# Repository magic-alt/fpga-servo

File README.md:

# fpga-servo

FPGA-based single-axis PMSM/BLDC servo-drive daughterboard for the ALINX AX7010 / Zynq-7000 (2022 board, active PL connector J10).

> **Four-layer engineering CAD — 2026-10-19; manufacturing hold.** Both ADC variants now have synchronized schematics and four-layer PCBs, independent BOMs and portable local libraries/models. Current candidates have zero native ERC/DRC violations, unconnected items and schematic-parity differences; eight Kelvin paths, bounded package escapes, free-corner checks, whole-board reserved-ground-layer checks and maximum ADC-body digital-copper exclusion pass. These are CAD results. Human engineering reviews and exact material/manufacturing-process acceptance remain open; neither board is approved for fabrication or full-power operation. See the [dual-board review](docs/reviews/dual_prototype_2026-10-18/README.md) and [release gates](docs/release_gates.md).

## 两种 ADC 方案

原方案使用 **ADS8588SIPM**；新方案使用 **AD7606C-16BSTZ**，采用四路 DOUT、电平转换和独立 XDC。AD7606C 的 1 MSPS、0–5 V 高速模式典型相位延迟及读取预算见[选型与迁移规格](docs/adc_high_performance_reselection_2026-10-12.md)和[FPGA 接口草案](hardware/ad7606c_servo/ad7606c_fast_candidate_profile_2026-10-12.json)。这些是器件及接口设计依据，实际闭环带宽仍须由 RTL、时序和整机测量验证。

**当前双方案：** [ADS8588S 原方案](hardware/ads8588s_servo/README.md) 与 [AD7606C 新方案](hardware/ad7606c_servo/README.md) 分目录维护，各有原理图、BOM、XDC 和 PCB。两方案新增独立 DC-link 子页，并修正编码器接收器引脚、栅极电阻和辅助电源；本轮电气 ECO 后两板已完成同步、整板布线及原生 DRC/图板一致性验收；工程签核与材料/特殊工艺接受仍开放。[最终工程审阅包](docs/reviews/dual_prototype_2026-10-18/manufacturing_review_packet.md)记录实际导出、校验和剩余门禁。通过[硬件入口](hardware/README.md)选择工程。

## Rev.A-P prototype design basis

| Item | Current design (not yet qualified) |
| --- | --- |
| Input / switching | DC 24–48 V; 20 kHz six-command PWM from AX7010 PL |
| Current / cooling | 10 A RMS continuous phase; 20 A instantaneous phase amplitude for 30 s, balanced sine (14.142 Arms); repetition/cooldown still to be qualified; 40 °C max ambient; forced air |
| Inverter | Six 100 V BSC040N10NS5 MOSFETs; **non-inverting DRV8300DPWR** with internal bootstrap diodes |
| Current sensing | Three motor-phase 5 mΩ / 3 W inline shunts with INA240A1DR (20 V/V); separate positive DC-bus 2 mΩ / 3 W shunt with INA240A1DR |
| Hardware OCP | LM393LVDDFR positive-bus comparator, nominal +25 A trip; hardware fault latch and six gated PWM inputs; **not reverse-current protection or a guaranteed maximum fault current** |
| ADC | Separate ADS8588S / AD7606C-16 projects; eight simultaneous 16-bit channels; three phase currents, VBUS, two board-mounted NTC inputs |
| Encoder | Differential 5 V ABZ interface using AM26LV32E; cable termination and power fault behavior still to qualify |
| Auxiliary power | LM5164 DC bus → 12 V, total continuous 1 A; TPS62901 → nominal 5.1 V, reviewed effective-capacitance budget and external soft start; VIO 3.3 V from AX7010 |
| DC-link / external sink | Ten individually damped 100 µF / 100 V branches; J7 protected-bus sink interface; no onboard brake; fixture qualification open |
| Power input | On-board 0456025.ER 25 A fuse, LM74502 + MOSFET polarity-protection stage (source fault-current coordination unqualified) |
| PCB | Both variants: four layers, 130 × 95 mm; JLC041621-3313 / NP-155F Tg155 candidate, outer 70 µm / inner 30 µm copper; material acceptance, paid Type VII POFV and controlled finished-hole processes remain open |

The driver is the **DRV8300D** non-inverting PW20 variant, **not** the older FD6288T or the DRV8300DI. The current-sense amplifiers are **INA240A1**, not INA241A2. The unused AX7010 J2 connector and old phase-window OCP have been removed. The LM74502 input circuit does not establish reverse regeneration blocking; there is no fitted brake or verified sink for regenerated motor energy.

## Review, cost and qualification

- [Rev.A simplified architecture and production review](docs/rev_a_simplified_design_production_review_2026-10-11.md): retain/replace/remove decisions, fault-coverage boundaries, cost tradeoffs, ECO sequence and G0–G5 release requirements.
- [68-group Rev.A sourcing-cost/ECO matrix](hardware/ads8588s_servo/reva_cost_eco_2026-10-11.csv): selected manufacturer part numbers, LCSC codes, extended cost, production concerns and priorities. Based on **2026-10-10 snapshot**, approximately **CNY 164.67 per board** for 148 purchased fitted references, excluding PCB/assembly/tax/shipping. Supplier stock and prices must be refreshed before any order.
- [Current sourcing selection](docs/lcsc_sourcing_review_2026-10-10.md), [architecture](docs/architecture.md), [design calculations](docs/design_calculations.md), [fabrication gates](docs/release_gates.md), and [hardware handoff](hardware/README.md).
- [ADS8588S AX7010 dual-serial timing contract](docs/adc_fpga_timing_and_freeze_2026-10-12.md) and [schematic/part freeze status](docs/reva_schematic_component_freeze_matrix_2026-10-12.md). For 20 kHz PWM the selected ADC uses 8-channel simultaneous sampling, two serial data lanes, 64 SCLK per frame, and a proposed 10 MHz initial SCLK; **data-rate and analog filter latency are independent concerns**.

**Release blockers:** complete source-bound component/footprint/electrical/thermal/layout/mechanical/DFM reviews and exact material/process acceptance. Physical qualification remains NOT_RUN: hot-inductance/startup and total 12 V/1 A loading, shunts/connectors/cooling, gate-driver and fault-to-VGS-off timing, supply sequencing/ADC validity, 10 Arms thermal soak and external regeneration containment. Historical CAD passes never replace fresh checks after an ECO.

## Repository layout

- `hardware/`: separate `ads8588s_servo/` and `ad7606c_servo/` KiCad projects with their own hierarchy, libraries, BOM and four-layer PCB. Original board/source snapshots are preserved; both current boards remain unreleased.
- Interface XDC and ADC configuration files live beside their hardware projects; this repository contains no HDL implementation.
- `docs/`: architecture, sizing calculations, schematic/PCB reviews, procurement evidence and release checklist.
- `tools/`: repository checks, layout review, native KiCad audit helpers and qualification scripts.
- `.github/workflows/`: static/native review workflows. **Passing CI/ERC alone is not a manufacturing or electrical safety release.**

See [AGENTS.md](AGENTS.md) before making an electrical edit. Implement all hardware ECOs on a separate branch with fresh native KiCad netlist/physical-pin comparison, ERC, DRC and bench qualification; do not replace the current board based on a document-only review.

## 开发与验证入口

当前工具统一为 `python tools/pcb.py`，按工程配置执行检查、原生验证、导出和开发预览。新增板卡优先增加配置和领域规则，不新建一套独立检查脚本。

```sh
python tools/pcb.py check --project ads8588s --scope schematic
python tools/pcb.py check --project ad7606c --scope schematic
python tools/pcb.py test --lane static
```

详见 [文档索引](docs/README.md)、[使用说明](docs/pcb_toolkit.md)、[新 PCB 接入](docs/pcb_toolkit_extension.md)；已替代的过程文档见 [归档](docs/archive/README.md)。

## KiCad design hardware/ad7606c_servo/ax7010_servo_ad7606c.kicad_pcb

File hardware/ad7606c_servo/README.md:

# AX7010 + AD7606C-16 四层工程板

## PWM safety gate ECO — 2026-10-20

U8–U11 retain independent hardware inhibition; R56–R61 now use 10 kΩ. The current [PWM_SAFETY_GATE review](../../docs/pwm_safety_gate_review_2026-10-20.md) supersedes earlier resistor/source hashes. Regenerate and review manufacturing outputs before fabricating this ECO; controlled restart RTL and dynamic qualification remain OPEN.

2026-10-20：按用户确认取消整页板载 DC-link 电容和阻尼器件，仅保留 J7 外部电容/泄放接口，已同步原理图、PCB、BOM 和验证合同。新鲜 ERC/DRC/未连接/图板差异均为 0；当时制造复审导出通过（PWM ECO 前，需重新生成/审核）。见[外置 DC-link 改版及证据](../../docs/reviews/ad7606c_jlc_2026-10-20/external_dc_link.md)。材料/特殊工艺接受、工程签核与实物资格仍开放。

2026-10-19 历史修复：四层 PCB 完成 U7、当时的 DC-link/J7、12 V 总负载 1 A、5 V 有效容量/软启动、装配焊盘、ADC 本体旁扇出及关键回路修复。八路 Kelvin、严格局部逃线、自由直角和 ADC 最大 10.2 mm 本体数字铜路检查在本次改版后重新通过。**人工工程审核、材料/特殊工艺接受和制造放行仍开放，禁止直接投板。**

打开 [KiCad 工程](ax7010_servo_ad7606c.kicad_pro) 或 [PCB](ax7010_servo_ad7606c.kicad_pcb)。当前源摘要见[门控 ECO 证据](../../docs/reviews/pwm_safety_gate_2026-10-20/summary.json)，外置 DC-link 的历史制造输出与变更见[当时摘要](../../docs/reviews/ad7606c_jlc_2026-10-20/external_summary.json)。[历史采用证明](../../docs/reviews/dual_prototype_2026-10-18/ad7606c_pcb_adoption_final.json)及[来源转换](../../docs/reviews/dual_prototype_2026-10-18/layout_adoption_transition.json)继续保留，没有取消 ADS8588S 原方案保存检查。

- 原生源：11 页、182 元件 / 162 网络 / 674 引脚归属，包含 DNP 和板外 J6。
- 采购实装：171 项；五个测试点为 PCB 裸铜，不进入装配 BOM/CPL。
- J7 为唯一外部 DC-link 接口，1 脚正极、2 脚 GND；外部电容及并联泄放电阻不在本板 BOM。连接及参考参数见[外部网络合同](../../docs/reviews/ad7606c_jlc_2026-10-20/external_dc_link.md)。
- U6：AD7606C-16BSTZ；AVCC/VDRIVE 同源 VA_5V，U27–U29 为 TXU0204PWR，OE 跟随 PWR_READY。四 DOUT、软件模式、配置/新帧有效合同见[电气方案](development_board.md)、`adc_profile.json` 与独立 XDC。
- 板框中心线 130 × 95 mm，原 H1–H4 及 J1/J3/J4/J5 锚点保留；安装孔为 3.2 mm PTH / 5 mm 铜焊盘。
- 原生叠构为 JLC041621-3313 / NP-155F Tg155 候选，外 70 µm / 内 30 µm 铜、ENIG。Tg155 与初始未证实的 Tg170 目标不同；材料接受、付费四层 Type VII POFV 和指定成品孔公差仍需关闭。
- 便携模型、许可和橙色 NOT OEM 净空模型见 [mechanical/](mechanical/README.md)。未知实际座高、配合端、线缆、工具和机箱仍为 OPEN。

设计目标：24–48 V、20 kHz、10 Arms 连续相电流、20 A 瞬时正弦相电流幅值 30 s（14.142 Arms）、40°C 强迫风冷；12 V **总**连续负载 1 A，含下游电源输入。静态预算不是满载启动、热或动态保证。没有板载制动；电机操作前必须独立验证外部吸能/钳位，J7 绕过输入 F1，外部支路自行保护。全部物理试验为 NOT_RUN。

从仓库根目录运行：

```sh
python tools/pcb.py check --project ad7606c --scope schematic
python tools/pcb.py verify --project ad7606c --scope prototype
python tools/pcb.py test --lane all --kicad-cli kicad-cli --pcb-python <KiCad-python>
```

完整几何验收使用带 `pcbnew` 的 KiCad Python；统一入口参数和缺失能力处理见[工具说明](../../docs/pcb_toolkit.md)。`prototype` 保留七项人工审核，缺少签核时应明确 BLOCKED；完整 `pcb_release` 及投板后的动态/热资格单独验收。

当前证据入口：[双方案审核](../../docs/reviews/dual_prototype_2026-10-18/README.md)、[逐器件覆盖](../../docs/reviews/dual_prototype_2026-10-18/component_coverage.md)、[发布门禁](../../docs/release_gates.md)、[低能量上电](../../docs/bringup.md)。`evidence/` 下日期为 2026-10-18 的初次建板、旧原理图 PDF 和旧布线验收属于电气 ECO 前历史，不可替代当前哈希的验证。

本仓库没有 HDL/固件实现。ADC 器件性能、候选高速配置和外部时序约束不代表已验证的 RTL/STA 或闭环带宽；不得把原 ADS 的 MPN 直接替换成 AD7606C。原方案及旧快照见 [ADS8588S 工程](../ads8588s_servo/README.md)。

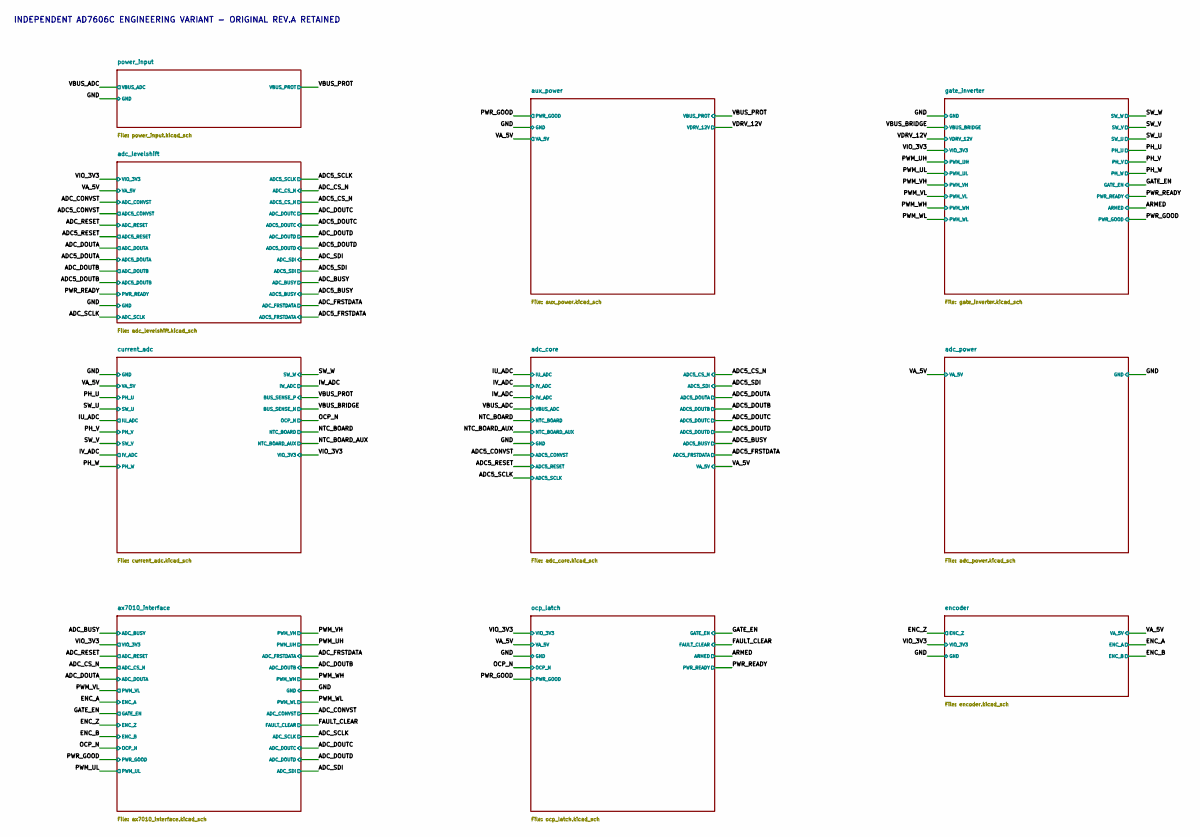
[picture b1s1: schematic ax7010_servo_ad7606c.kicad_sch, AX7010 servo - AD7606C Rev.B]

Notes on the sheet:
INDEPENDENT AD7606C ENGINEERING VARIANT - ORIGINAL REV.A RETAINED

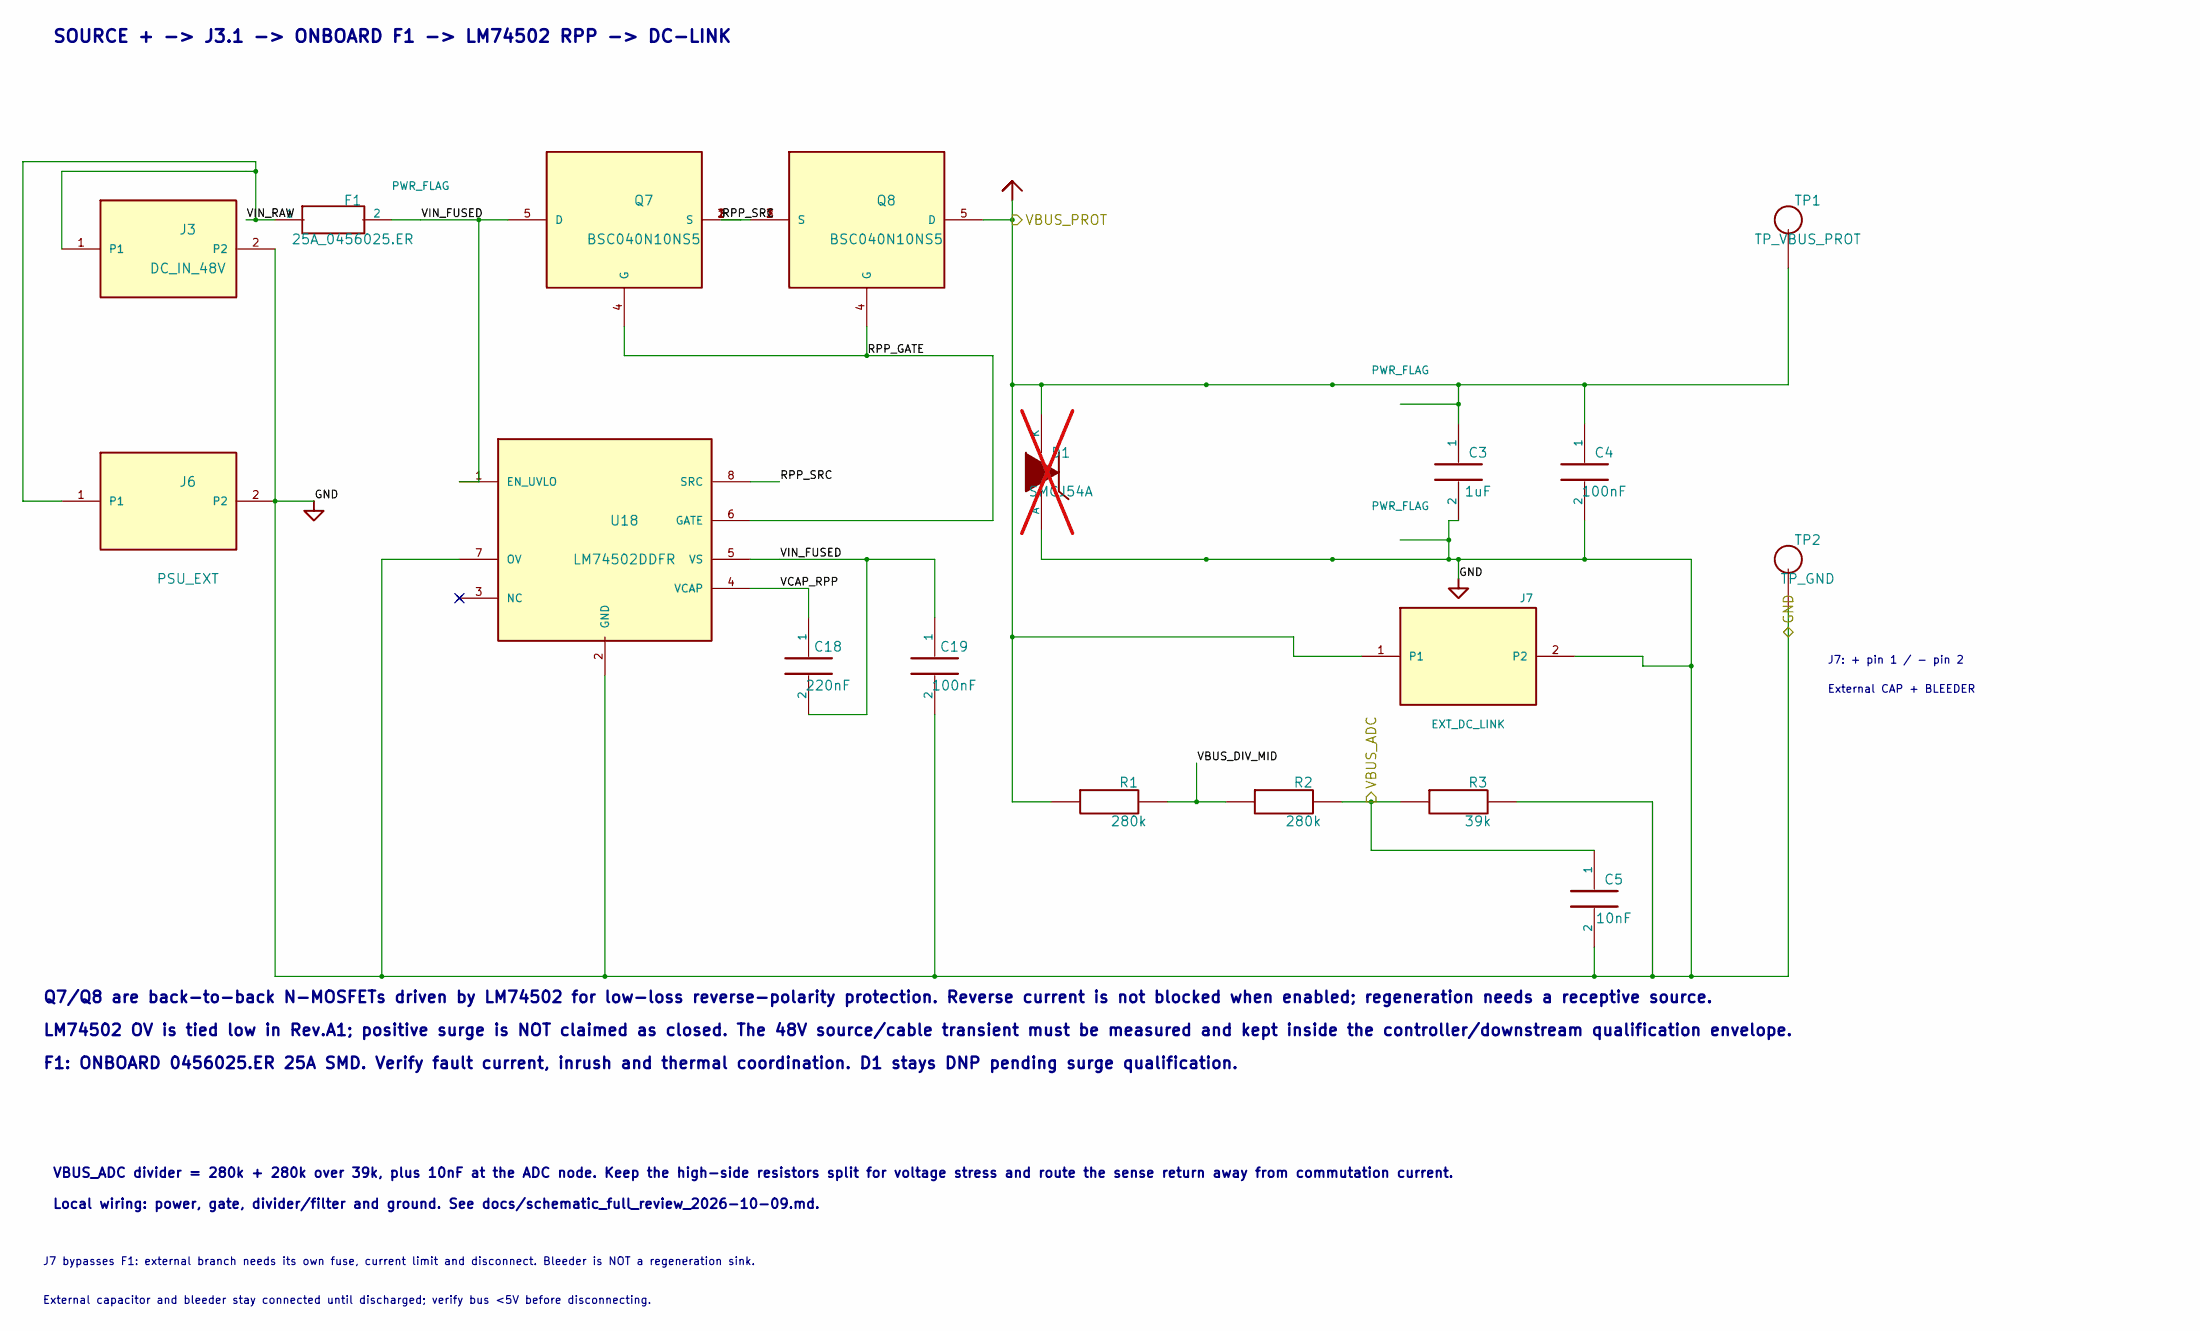
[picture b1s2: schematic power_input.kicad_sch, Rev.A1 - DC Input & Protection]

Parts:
C3: 1uF; C_Rect_L18.0mm_W8.0mm_P15.00mm_FKS3_FKP3; MPN C212E105J6BC000; LCSC C604836
C4: 100nF; C_1812_4532Metric; MPN C4532C0G2A104JT000N; LCSC C342611
C5: 10nF; C_0603_1608Metric; MPN 0603B103K101NT; LCSC C43253
C18: 220nF; C_0805_2012Metric; MPN 0805B224K500NT; LCSC C163697
C19: 100nF; C_0805_2012Metric; MPN 0805B104K101NT; LCSC C89258
D1: SMCJ54A; D_SMC; not fitted
F1: 25A_0456025.ER; Littelfuse_456_25A_SMD; MPN 0456025.ER; LCSC C315877
J3: DC_IN_48V; PhoenixContact_MKDS_5_2_9.52mm; MPN 1714971; LCSC C92145
J6: PSU_EXT; MPN TBD
J7: EXT_DC_LINK; PhoenixContact_MKDS_5_2_9.52mm; MPN 1714971; LCSC C92145
Q7, Q8: BSC040N10NS5; Infineon_PG-TDSON-8_6.15x5.15mm; MPN BSC040N10NS5; LCSC C534334
R1, R2: 280k; R_0805_2012Metric; MPN PTFR0805B280KP9; LCSC C2849140
R3: 39k; R_0603_1608Metric; MPN TC0325B3902T5F; LCSC C2988897
TP1: TP_VBUS_PROT; TestPoint_Pad_D2.0mm
TP2: TP_GND; TestPoint_Pad_D2.0mm
U18: LM74502DDFR; TI_DDF0008A_SOT23_8_P0.65mm; MPN LM74502DDFR; LCSC C3236215

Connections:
/GND: C3.2, C4.2, C5.2, C19.2, D1.2 (A), J3.2, J6.2, J7.2, R3.2, TP2.1 (1_1), U18.2 (GND), U18.7 (OV); also elsewhere on the board
/VBUS_ADC: C5.1, R2.2, R3.1; also elsewhere on the board
/VBUS_PROT: C3.1, C4.1, D1.1 (K), J7.1, Q8.5 (D), R1.1, TP1.1 (1_1); also elsewhere on the board
/power_input/RPP_GATE: Q7.4 (G), Q8.4 (G), U18.6 (GATE)
/power_input/RPP_SRC: Q7.1 (S), Q7.2 (S), Q7.3 (S), Q8.1 (S), Q8.2 (S), Q8.3 (S), U18.8 (SRC)
/power_input/VBUS_DIV_MID: R1.2, R2.1
/power_input/VCAP_RPP: C18.1, U18.4 (VCAP)
/power_input/VIN_FUSED: C18.2, C19.1, F1.2, Q7.5 (D), U18.1 (EN_UVLO), U18.5 (VS)
/power_input/VIN_RAW: F1.1, J3.1, J6.1

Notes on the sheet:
Local wiring: power, gate, divider/filter and ground. See docs/schematic_full_review_2026-10-09.md.
LM74502 OV is tied low in Rev.A1; positive surge is NOT claimed as closed. The 48V source/cable transient must be measured and kept inside the controller/downstream qualification envelope.
VBUS_ADC divider = 280k + 280k over 39k, plus 10nF at the ADC node. Keep the high-side resistors split for voltage stress and route the sense return away from commutation current.
F1: ONBOARD 0456025.ER 25A SMD. Verify fault current, inrush and thermal coordination. D1 stays DNP pending surge qualification.
Q7/Q8 are back-to-back N-MOSFETs driven by LM74502 for low-loss reverse-polarity protection. Reverse current is not blocked when enabled; regeneration needs a receptive source.
SOURCE + -> J3.1 -> ONBOARD F1 -> LM74502 RPP -> DC-LINK
J7: + pin 1 / - pin 2
J7 bypasses F1: external branch needs its own fuse, current limit and disconnect. Bleeder is NOT a regeneration sink.
External capacitor and bleeder stay connected until discharged; verify bus <5V before disconnecting.
External CAP + BLEEDER

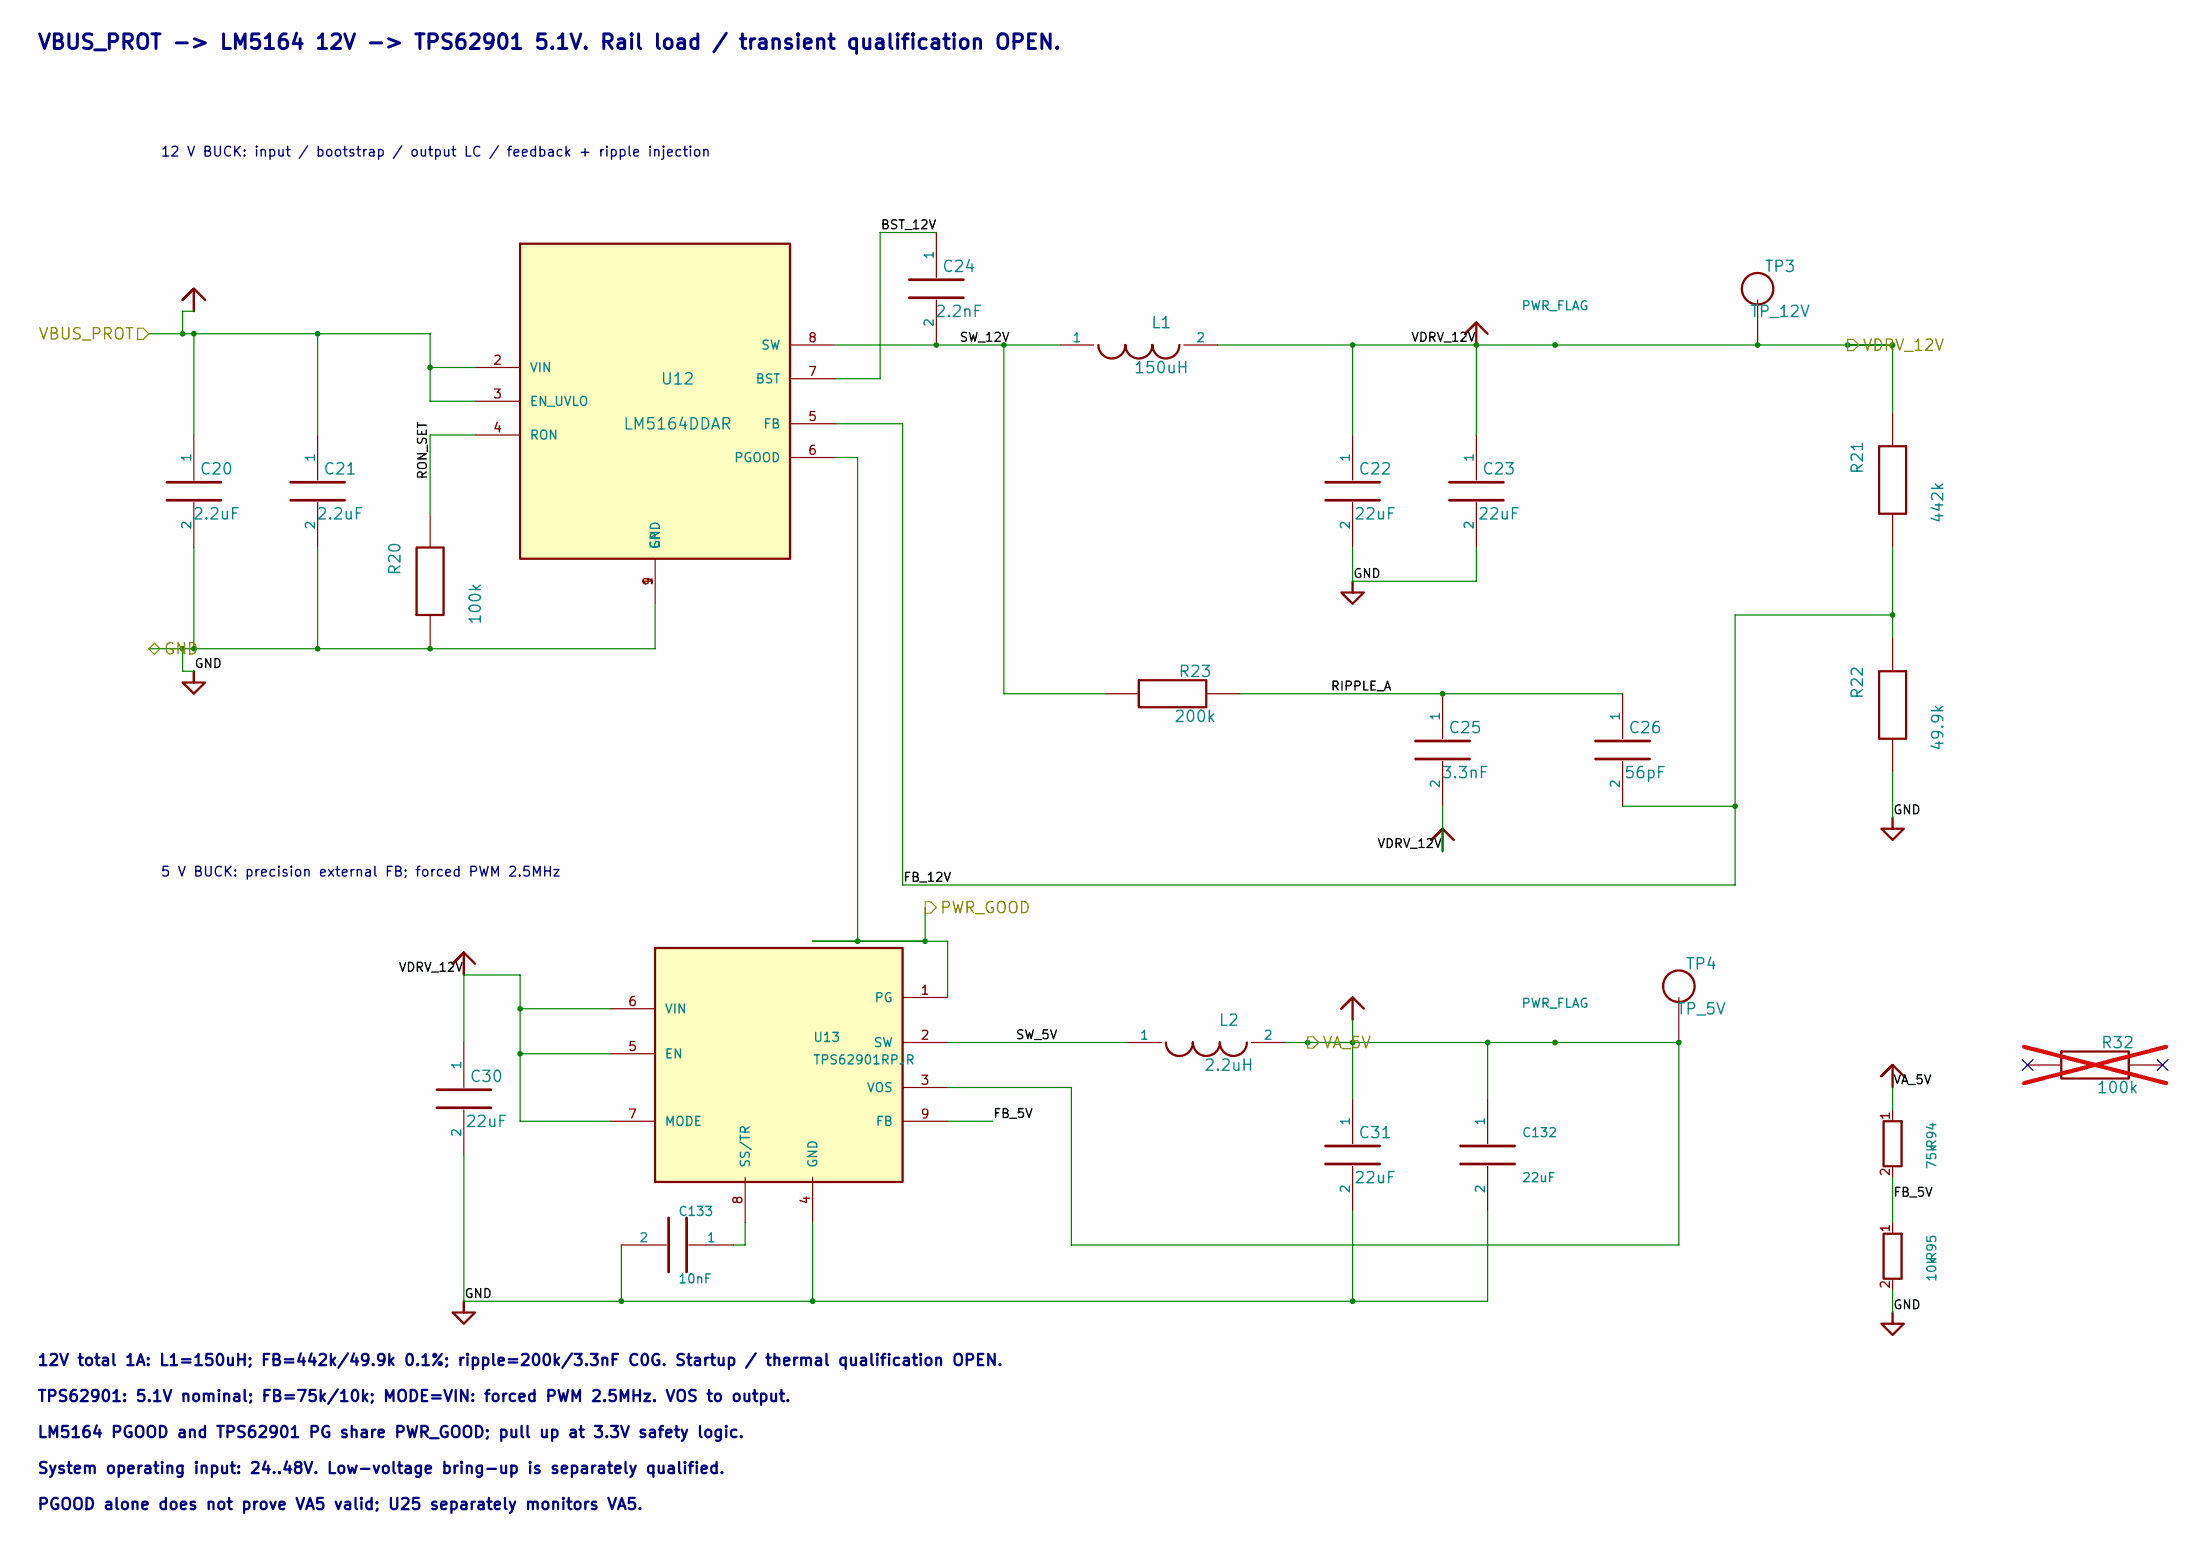
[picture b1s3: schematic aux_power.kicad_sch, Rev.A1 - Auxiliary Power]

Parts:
C20, C21: 2.2uF; C_1210_3225Metric; MPN 1210B225K101NT; LCSC C42400139
C22, C23: 22uF; C_1210_3225Metric; MPN 1210B226K250NT; LCSC C5204920
C24: 2.2nF; C_0603_1608Metric; MPN 0603B222J500NT; LCSC C60328
C25: 3.3nF; C_0603_1608Metric; MPN GRM1885C1H332JA01D; LCSC C77036
C26: 56pF; C_0603_1608Metric; MPN 0603CG560J500NT; LCSC C1676
C30, C31, C132: 22uF; Murata_GRM32_1210; MPN GRM32ER71E226KE15L; LCSC C21397
C133: 10nF; C_0603_1608Metric; MPN 0603B103K101NT; LCSC C43253
L1: 150uH; Wurth_WE_PD_1210_7447709151; MPN 7447709151
L2: 2.2uH; Sunlord_SWPA4020S; MPN SWPA4020S2R2MT; LCSC C83423
R20: 100k; R_0603_1608Metric; MPN 0603WAF1003T5E; LCSC C25803
R21: 442k; R_0603_1608Metric; MPN RT0603BRD07442KL
R22: 49.9k; R_0603_1608Metric; MPN RT0603BRD0749K9L; LCSC C705780
R23: 200k; R_0603_1608Metric; MPN RC0603FR-07200KL; LCSC C105574
R32: 100k; R_0603_1608Metric; not fitted
R94: 75k; R_0603_1608Metric; Tolerance 0.05%; MPN PTFR0603Q75K0N9; LCSC C53280140
R95: 10k; R_0603_1608Metric; Tolerance 0.05%; MPN PTFR0603Q10K0N9; LCSC C51822132
TP3: TP_12V; TestPoint_Pad_D2.0mm
TP4: TP_5V; TestPoint_Pad_D2.0mm
U12: LM5164DDAR; TI_DDA0008B_LM5164; MPN LM5164DDAR; LCSC C477928
U13: TPS62901RPJR; Texas_RPJ0009A_VQFN-HR-9_1.5x2mm; MPN TPS62901RPJR; LCSC C2864847

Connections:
/GND: C20.2, C21.2, C22.2, C23.2, C30.2, C31.2, C132.2, C133.2, R20.1, R22.2, R95.2, U12.1 (GND), U12.9 (EP), U13.4 (GND); also elsewhere on the board
/PWR_GOOD: U12.6 (PGOOD), U13.1 (PG); also elsewhere on the board
/VA_5V: C31.1, C132.1, L2.2, R94.1, TP4.1 (1_1), U13.3 (VOS); also elsewhere on the board
/VBUS_PROT: C20.1, C21.1, U12.2 (VIN), U12.3 (EN_UVLO); also elsewhere on the board
/VDRV_12V: C22.1, C23.1, C25.2, C30.1, L1.2, R21.1, TP3.1 (1_1), U13.5 (EN), U13.6 (VIN), U13.7 (MODE); also elsewhere on the board
/aux_power/BST_12V: C24.1, U12.7 (BST)
/aux_power/FB_5V: R94.2, R95.1, U13.9 (FB)
/aux_power/FB_12V: C26.2, R21.2, R22.1, U12.5 (FB)
/aux_power/RIPPLE_A: C25.1, C26.1, R23.2
/aux_power/RON_SET: R20.2, U12.4 (RON)
/aux_power/SW_5V: L2.1, U13.2 (SW)
/aux_power/SW_12V: C24.2, L1.1, R23.1, U12.8 (SW)
unnamed: C133.1, U13.8 (SS/TR)

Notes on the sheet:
VBUS_PROT -> LM5164 12V -> TPS62901 5.1V. Rail load / transient qualification OPEN.
TPS62901: 5.1V nominal; FB=75k/10k; MODE=VIN: forced PWM 2.5MHz. VOS to output.
System operating input: 24..48V. Low-voltage bring-up is separately qualified.
PGOOD alone does not prove VA5 valid; U25 separately monitors VA5.
LM5164 PGOOD and TPS62901 PG share PWR_GOOD; pull up at 3.3V safety logic.
12V total 1A: L1=150uH; FB=442k/49.9k 0.1%; ripple=200k/3.3nF C0G. Startup / thermal qualification OPEN.
12 V BUCK: input / bootstrap / output LC / feedback + ripple injection
5 V BUCK: precision external FB; forced PWM 2.5MHz

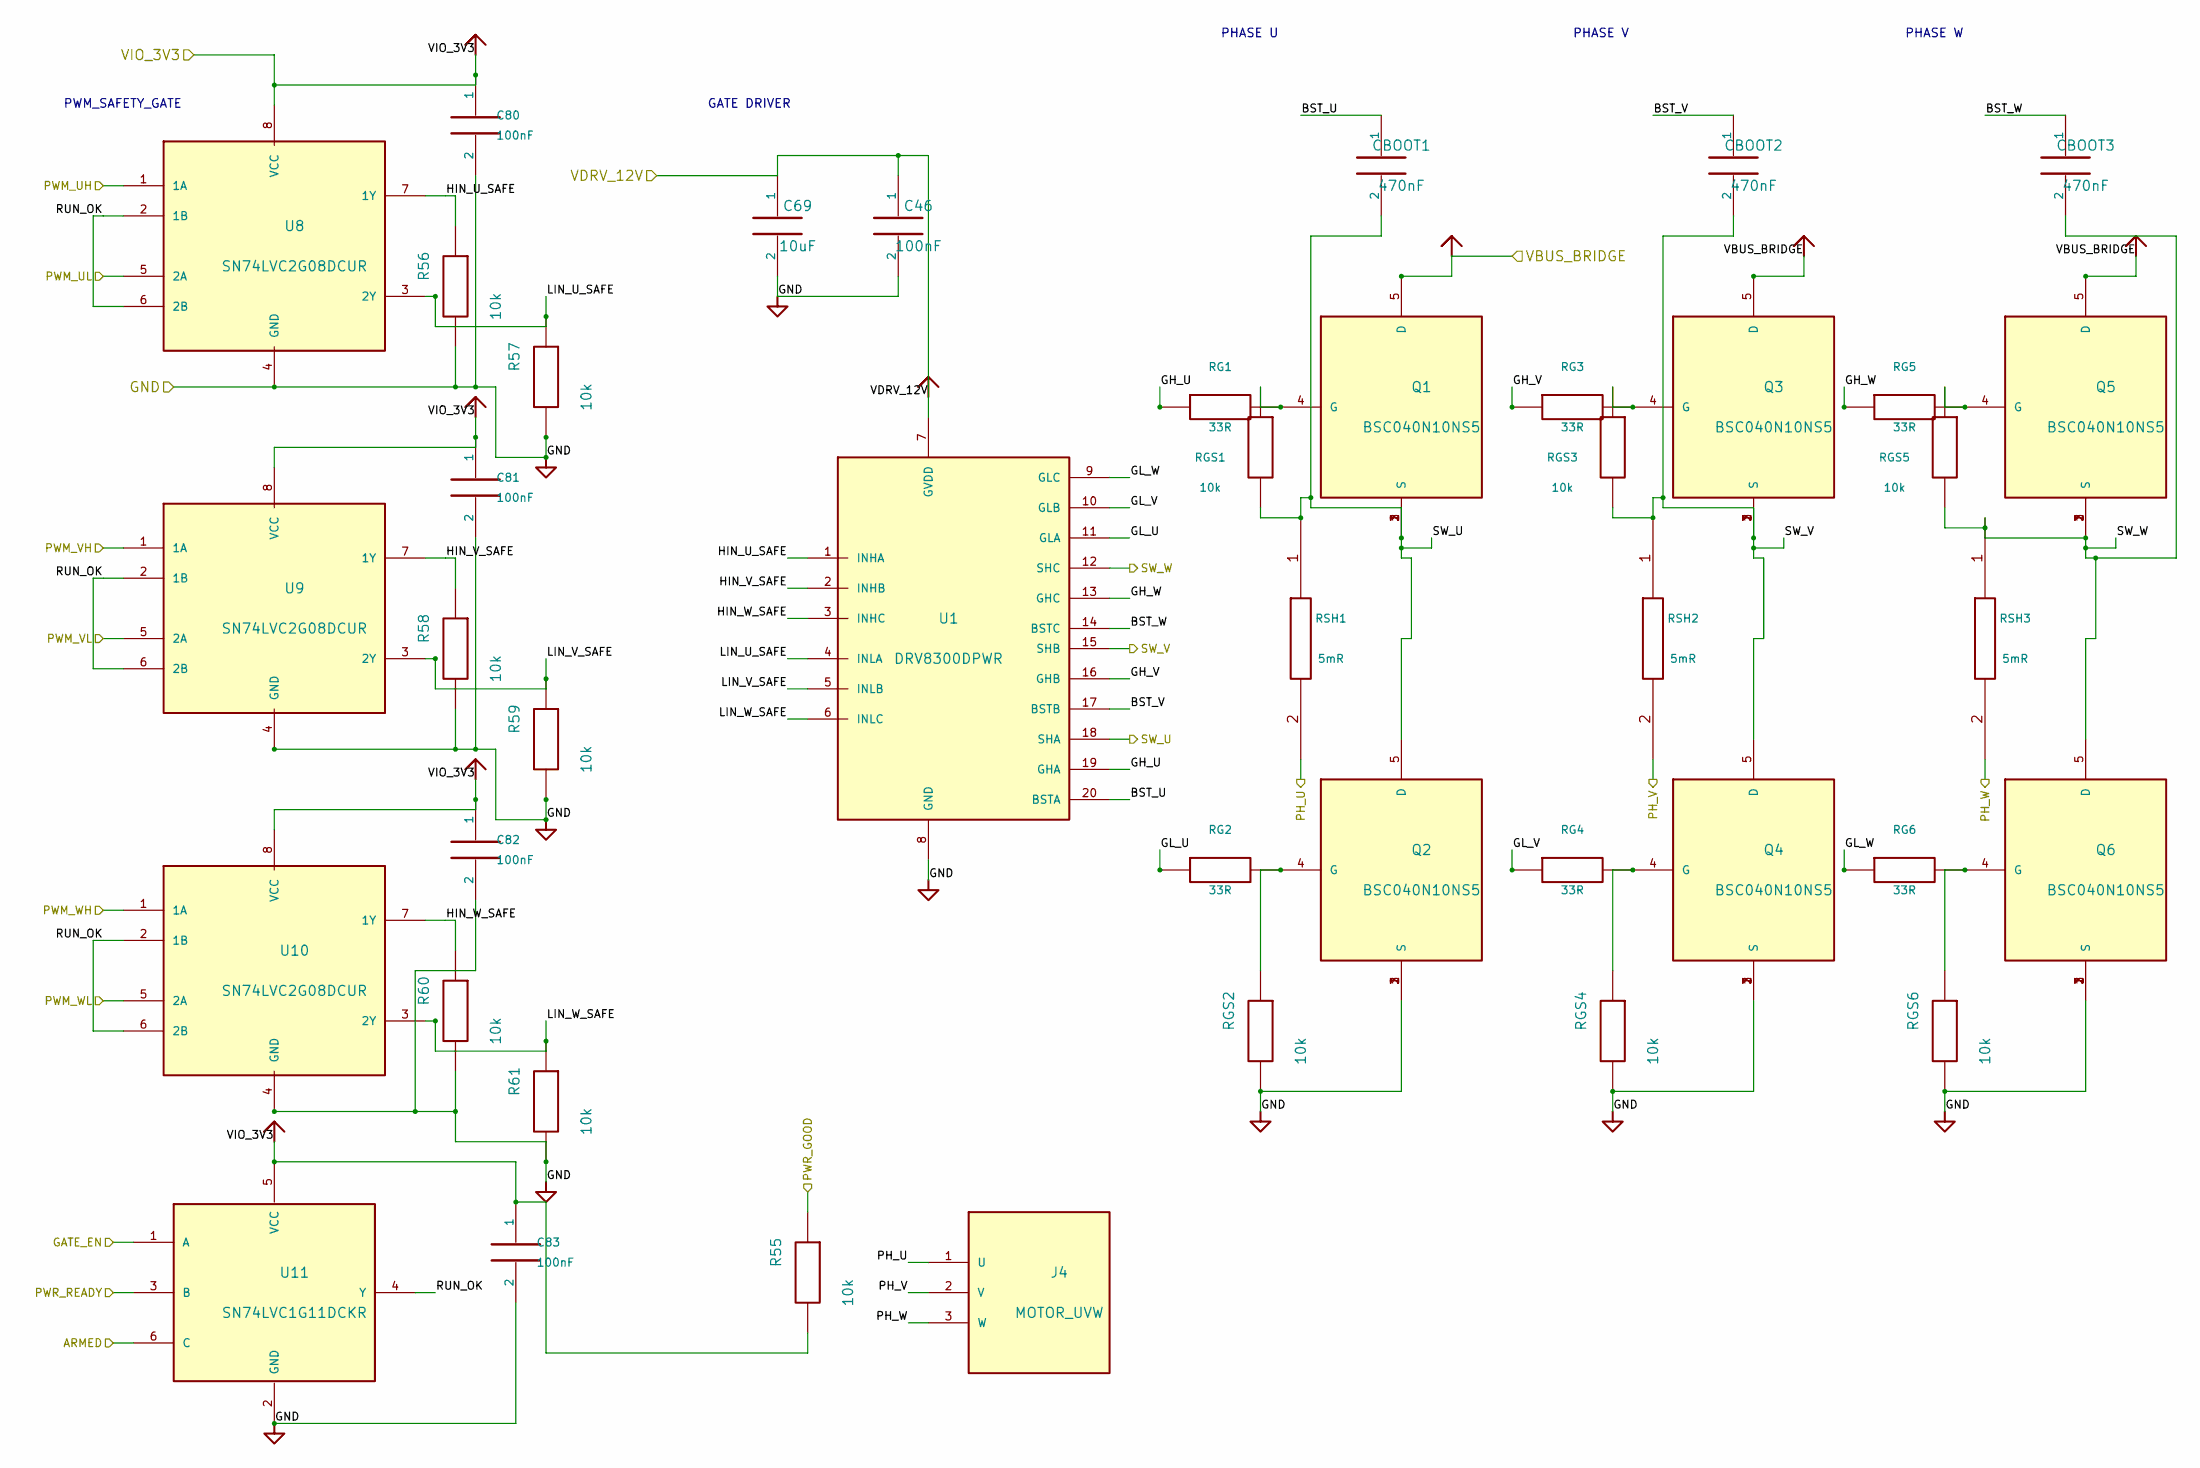
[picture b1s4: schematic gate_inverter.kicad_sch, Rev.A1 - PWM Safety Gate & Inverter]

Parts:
C46, C80, C81, C82, C83: 100nF; C_0603_1608Metric; MPN 0603B104K500NT; LCSC C30926
C69: 10uF; C_1206_3216Metric; MPN CGA1206X7R106K250NT; LCSC C6119987
CBOOT1, CBOOT2, CBOOT3: 470nF; C_0805_2012Metric; MPN 0805B474K500NT; LCSC C49955
J4: MOTOR_UVW; KEFA_KF950_3_9.50mm_D1.85; MPN KF950-9.5-3P; LCSC C475107
Q1, Q2, Q3, Q4, Q5, Q6: BSC040N10NS5; Infineon_PG-TDSON-8_6.15x5.15mm; MPN BSC040N10NS5; LCSC C534334
R55, R56, R57, R58, R59, R60, R61: 10k; R_0603_1608Metric; MPN ABD03K1002FT; LCSC C5139509
RG1, RG2, RG3, RG4, RG5, RG6: 33R; Vishay_CRCW0603_HP; MPN CRCW060333R0FKEAHP; LCSC UNVERIFIED
RGS1, RGS2, RGS3, RGS4, RGS5, RGS6: 10k; R_0603_1608Metric; MPN ABD03K1002FT; LCSC C5139509
RSH1, RSH2, RSH3: 5mR; HoYLR2512_Kelvin; MPN HoYLR2512-3W-5mR-1%; LCSC C5375461
U1: DRV8300DPWR; TSSOP-20_4.4x6.5mm_P0.65mm; MPN DRV8300DPWR; LCSC C3036056
U8, U9, U10: SN74LVC2G08DCUR; TI_DCU0008A_VSSOP8_P0.5mm; MPN SN74LVC2G08DCUR; LCSC C91875
U11: SN74LVC1G11DCKR; SOT-363_SC-70-6; MPN SN74LVC1G11DCKR; LCSC C529281

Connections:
/ARMED: U11.6 (C); also elsewhere on the board
/GATE_EN: U11.1 (A); also elsewhere on the board
/GND: C46.2, C69.2, C80.2, C81.2, C82.2, C83.2, Q2.1 (S), Q2.2 (S), Q2.3 (S), Q4.1 (S), Q4.2 (S), Q4.3 (S), Q6.1 (S), Q6.2 (S), Q6.3 (S), R56.2, R57.2, R58.2, R59.2, R60.2, R61.2, RGS2.2, RGS4.2, RGS6.2, U1.8 (GND), U8.4 (GND), U9.4 (GND), U10.4 (GND), U11.2 (GND); also elsewhere on the board
/PH_U: J4.1 (U), RSH1.2; also elsewhere on the board
/PH_V: J4.2 (V), RSH2.2; also elsewhere on the board
/PH_W: J4.3 (W), RSH3.2; also elsewhere on the board
/PWM_UH: U8.1 (1A); also elsewhere on the board
/PWM_UL: U8.5 (2A); also elsewhere on the board
/PWM_VH: U9.1 (1A); also elsewhere on the board
/PWM_VL: U9.5 (2A); also elsewhere on the board
/PWM_WH: U10.1 (1A); also elsewhere on the board
/PWM_WL: U10.5 (2A); also elsewhere on the board
/PWR_GOOD: R55.1; also elsewhere on the board
/PWR_READY: U11.3 (B); also elsewhere on the board
/SW_U: CBOOT1.2, Q1.1 (S), Q1.2 (S), Q1.3 (S), Q2.5 (D), RGS1.2, RSH1.1, U1.18 (SHA); also elsewhere on the board
/SW_V: CBOOT2.2, Q3.1 (S), Q3.2 (S), Q3.3 (S), Q4.5 (D), RGS3.2, RSH2.1, U1.15 (SHB); also elsewhere on the board
/SW_W: CBOOT3.2, Q5.1 (S), Q5.2 (S), Q5.3 (S), Q6.5 (D), RGS5.2, RSH3.1, U1.12 (SHC); also elsewhere on the board
/VBUS_BRIDGE: Q1.5 (D), Q3.5 (D), Q5.5 (D); also elsewhere on the board
/VDRV_12V: C46.1, C69.1, U1.7 (GVDD); also elsewhere on the board
/VIO_3V3: C80.1, C81.1, C82.1, C83.1, R55.2, U8.8 (VCC), U9.8 (VCC), U10.8 (VCC), U11.5 (VCC); also elsewhere on the board
/gate_inverter/BST_U: CBOOT1.1, U1.20 (BSTA)
/gate_inverter/BST_V: CBOOT2.1, U1.17 (BSTB)
/gate_inverter/BST_W: CBOOT3.1, U1.14 (BSTC)
/gate_inverter/GH_U: RG1.1, U1.19 (GHA)
/gate_inverter/GH_V: RG3.1, U1.16 (GHB)
/gate_inverter/GH_W: RG5.1, U1.13 (GHC)
/gate_inverter/GL_U: RG2.1, U1.11 (GLA)
/gate_inverter/GL_V: RG4.1, U1.10 (GLB)
/gate_inverter/GL_W: RG6.1, U1.9 (GLC)
/gate_inverter/HIN_U_SAFE: R56.1, U1.1 (INHA), U8.7 (1Y)
/gate_inverter/HIN_V_SAFE: R58.1, U1.2 (INHB), U9.7 (1Y)
/gate_inverter/HIN_W_SAFE: R60.1, U1.3 (INHC), U10.7 (1Y)
/gate_inverter/LIN_U_SAFE: R57.1, U1.4 (INLA), U8.3 (2Y)
/gate_inverter/LIN_V_SAFE: R59.1, U1.5 (INLB), U9.3 (2Y)
/gate_inverter/LIN_W_SAFE: R61.1, U1.6 (INLC), U10.3 (2Y)
/gate_inverter/RUN_OK: U8.2 (1B), U8.6 (2B), U9.2 (1B), U9.6 (2B), U10.2 (1B), U10.6 (2B), U11.4 (Y)
unnamed: Q1.4 (G), RG1.2, RGS1.1
unnamed: Q2.4 (G), RG2.2, RGS2.1
unnamed: Q3.4 (G), RG3.2, RGS3.1
unnamed: Q4.4 (G), RG4.2, RGS4.1
unnamed: Q5.4 (G), RG5.2, RGS5.1
unnamed: Q6.4 (G), RG6.2, RGS6.1

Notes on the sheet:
PWM_SAFETY_GATE
GATE DRIVER
PHASE U
PHASE V
PHASE W
